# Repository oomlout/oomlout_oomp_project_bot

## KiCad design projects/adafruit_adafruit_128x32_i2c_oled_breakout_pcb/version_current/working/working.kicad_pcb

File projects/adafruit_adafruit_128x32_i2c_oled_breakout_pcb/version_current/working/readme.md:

# OOMP Project  
## Adafruit-128x32-I2C-OLED-Breakout-PCB  by adafruit  
  
oomp key: oomp_projects_flat_adafruit_adafruit_128x32_i2c_oled_breakout_pcb  
(snippet of original readme)  
  
- PCB for the Adafruit 128x32 I2C OLED breakout board  
  
<a href="http://www.adafruit.com/products/931"><br/>Click here to purchase one from the Adafruit shop</a>  
  
__Format is EagleCAD schematic and board layout__  
  
These displays are small, only about 1" diagonal, but very readable due to the high contrast of an OLED display. This display is made of 128x32 individual white OLED pixels, each one is turned on or off by the controller chip. Because the display makes its own light, no backlight is required. This reduces the power required to run the OLED and is why the display has such high contrast; we really like this miniature display for its crispness!  

The driver chip SSD1306, __communicates via I2C only.__ 3 pins are required to communicate with the chip in the OLED display, two of which are I2C data/clock pins.  
  
The OLED and driver require a 3.3V power supply and 3.3V logic levels for communication. To make it easier for our customers to use, we've added a 3.3v regulator and level shifter on board! This makes it compatible with any 5V microcontroller, such as the Arduino.  
  
The power requirements depend a little on how much of the display is lit but on average the display uses about 20mA from the 3.3V supply. Built into the OLED driver is a simple switch-cap charge pump that turns 3.3v-5v into a high voltage drive for the OLEDs, making it one of the easiest ways to get an OLED into your project!  
  
Of course, we wouldn't leave  
  full source readme at [readme_src.md](readme_src.md)  
  
source repo at: [https://github.com/adafruit/Adafruit-128x32-I2C-OLED-Breakout-PCB](https://github.com/adafruit/Adafruit-128x32-I2C-OLED-Breakout-PCB)  
## Board  

## Schematic  

[schematic pdf](working_schematic.pdf)  
## Images

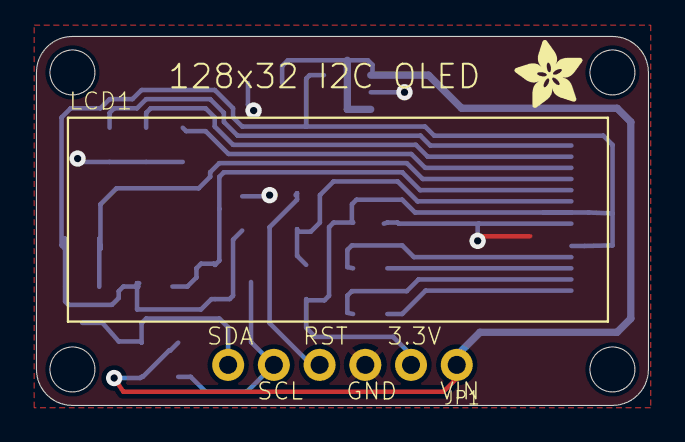
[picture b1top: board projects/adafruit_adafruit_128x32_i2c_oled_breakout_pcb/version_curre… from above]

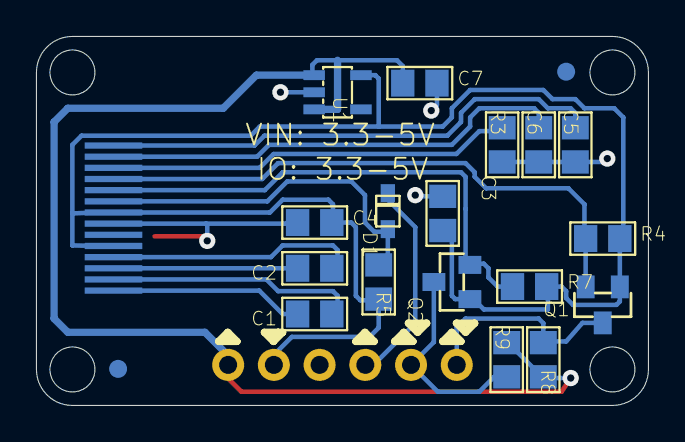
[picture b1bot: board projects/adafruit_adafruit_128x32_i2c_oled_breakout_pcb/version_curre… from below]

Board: 2 copper layers, 34.0 x 20.5 mm, 26 parts (19 on the bottom side), 16 nets.

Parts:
@HOLE0, @HOLE1, @HOLE2, @HOLE3: (no value)
C1, C2, C3, C4: 1uF; 0805
C5, C6, C7: 10uF; 0805
D1: 1N4148; SOD-323F
FID1, FID2: FIDUCIAL""; FIDUCIAL_1MM
JP1: 1X06_ROUND_70
LCD1: UG-2832HSWEG02_WRAPUNDER
Q1, Q2: BSS138; SOT23-WIDE
R3: 390K; 0805
R4, R5, R7, R8, R9: 10K; 0805
U1: RT9193; SOT23-5
U$16: ADAFRUIT_3.5MM

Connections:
3.3V: C3.2, C4.2, JP1.2, LCD1.5, LCD1.8, Q1.1, Q2.1, R4.2, R5.2, R7.2, U1.5
GND: C3.1, C4.1, C5.1, C6.1, C7.2, JP1.3, LCD1.7, R3.1, U1.2
unnamed: C1.2, LCD1.1
unnamed: C1.1, LCD1.2
unnamed: C2.2, LCD1.3
unnamed: C2.1, LCD1.4
unnamed: C6.2, LCD1.13
unnamed: C5.2, LCD1.14
unnamed: LCD1.12, R3.2
RES_3.3V: D1.A, LCD1.9, R5.1
RES_5.0V: D1.C, JP1.4
SCL_3.3V: LCD1.10, Q2.2, R7.1
SCL_5.0V: JP1.5, Q2.3, R9.1
SDA_3.3V: LCD1.11, Q1.2, R4.1
SDA_5.0V: JP1.6, Q1.3, R8.1
VIN: C7.1, JP1.1, R8.2, R9.2, U1.1, U1.3

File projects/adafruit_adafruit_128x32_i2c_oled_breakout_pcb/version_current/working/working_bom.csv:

"Id";"Designator";"Footprint";"Quantity";"Designation";"Supplier and ref";
1;"LCD1";"UG-2832HSWEG02_WRAPUNDER";1;"";;;
2;"@HOLE3,@HOLE0,@HOLE2,@HOLE1";"";4;"";;;
3;"JP1";"1X06_ROUND_70";1;"";;;
4;"U$16";"ADAFRUIT_3.5MM";1;"";;;
5;"C5,C7,C6";"0805";3;"10uF";;;
6;"C4,C3,C2,C1";"0805";4;"1uF";;;
7;"R3";"0805";1;"390K";;;
8;"FID1,FID2";"FIDUCIAL_1MM";2;"FIDUCIAL""";;;
9;"R5,R8,R4,R7,R9";"0805";5;"10K";;;
10;"D1";"SOD-323F";1;"1N4148";;;
11;"Q1,Q2";"SOT23-WIDE";2;"BSS138";;;
12;"U1";"SOT23-5";1;"RT9193";;;

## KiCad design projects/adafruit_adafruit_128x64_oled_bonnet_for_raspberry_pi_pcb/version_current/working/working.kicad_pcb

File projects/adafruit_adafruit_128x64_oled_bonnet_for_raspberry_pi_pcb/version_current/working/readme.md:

# OOMP Project  
## Adafruit-128x64-OLED-Bonnet-for-Raspberry-Pi-PCB  by adafruit  
  
oomp key: oomp_projects_flat_adafruit_adafruit_128x64_oled_bonnet_for_raspberry_pi_pcb  
(snippet of original readme)  
  
-- Adafruit 128x64 OLED Bonnet for Raspberry Pi PCB  
  
<a href="http://www.adafruit.com/products/3531"><br/>  
Click here to purchase one from the Adafruit shop</a>  
  
PCB files for the Adafruit 128x64 OLED Bonnet for Raspberry Pi. Format is EagleCAD schematic and board layout  
  
For more details, check out the product page at  
* http://www.adafruit.com/product/3531  
  
--- Description  
  
If you'd like a compact display, with buttons and a joystick - we've got what you're looking for. The Adafruit 128x64 OLED Bonnet for Raspberry Pi is the big sister to our mini PiOLED add-on. This version has 128x64 pixels (instead of 128x32) and a much larger screen besides. With the OLED display in the center, we had some space on either side so we added a 5-way joystick and two pushbuttons. Great for when you want to have a control interface for your project.  
  
These displays are small, only about 1.3" diagonal, but very readable due to the high contrast of an OLED display. This screen is made of 128x64 individual white OLED pixels and because the display makes its own light, no backlight is required. This reduces the power required to run the OLED and is why the display has such high contrast; we really like this miniature display for its crispness!  
  
Please note that this display is too small to act as a primary display for the Pi (e.g. it can't act like or display what would normally be on the HDMI screen). Instead, we recommend using pygame for drawi  
  full source readme at [readme_src.md](readme_src.md)  
  
source repo at: [https://github.com/adafruit/Adafruit-128x64-OLED-Bonnet-for-Raspberry-Pi-PCB](https://github.com/adafruit/Adafruit-128x64-OLED-Bonnet-for-Raspberry-Pi-PCB)  
## Board  

## Schematic  

[schematic pdf](working_schematic.pdf)  
## Images

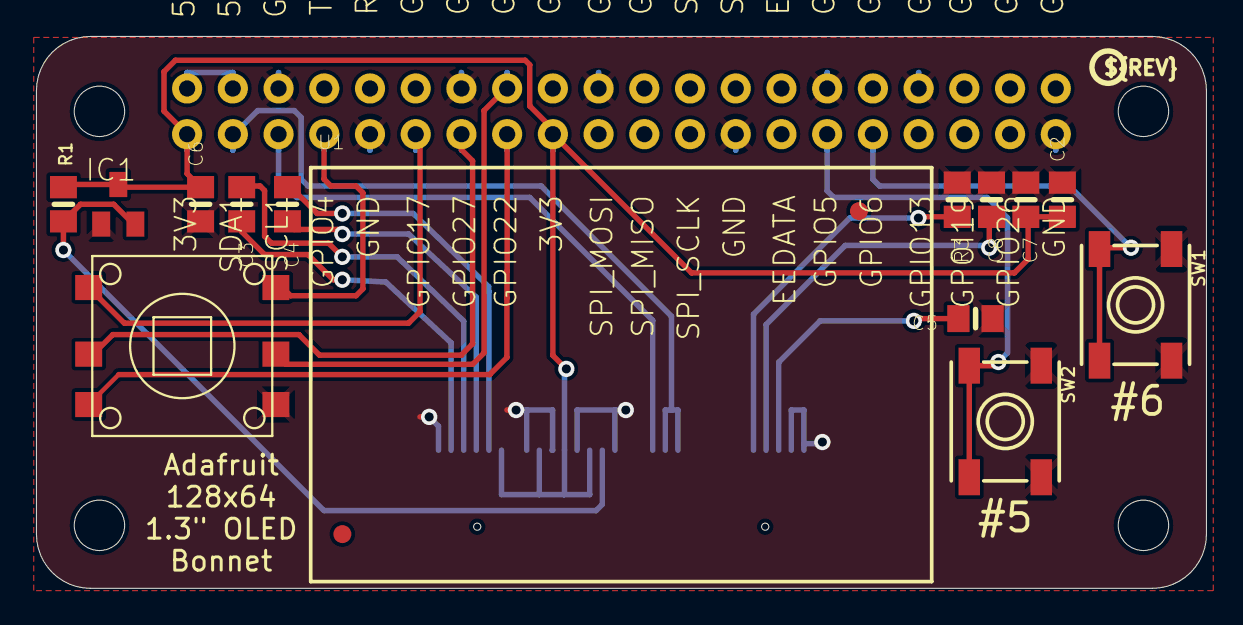
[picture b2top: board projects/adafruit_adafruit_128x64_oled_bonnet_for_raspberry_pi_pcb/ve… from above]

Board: 2 copper layers, 65.0 x 30.7 mm, 18 parts (0 on the bottom side), 20 nets.

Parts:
C2, C5: 10uF; 0805-NO
C3, C4, C6, C7, C8: 2.2uF; 0805-NO
FID1, FID2: FIDUCIAL_1MM
IC1: APX803; SOT23
R1: 10K; 0805-NO
R3: 390K; 0805-NO
RPI1: RASPBERRYPI_BPLUS_BONNET_THMSMT; PI_BONNET_THMSMT
SW1, SW2: EVQQ; EVQ-Q2_SMALLER
SW3: NAVSWITCHSKQUABAUE010; SKQUBAE010
U1: UG-2864HSWEG01; UG-2864HSWEG01_1.3_WRAPAROUND
U$2: PCBFEAT-REV-040

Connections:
3.3V: C2.1, C6.2, C7.2, IC1.3, R1.2, RPI1.1, RPI1.17, RPI1.S1, RPI1.S17, U1.6, U1.9, U1.11, U1.13
5.0V: RPI1.2, RPI1.4, RPI1.S2, RPI1.S4
GND: C2.2, C5.1, C6.1, C7.1, C8.1, IC1.1, R3.1, RPI1.6, RPI1.9, RPI1.14, RPI1.20, RPI1.25, RPI1.30, RPI1.34, RPI1.39, RPI1.S6, RPI1.S9, RPI1.S14, RPI1.S20, RPI1.S25, RPI1.S30, RPI1.S34, RPI1.S39, SW1.B, SW1.B', SW2.B, SW2.B', SW3.4, U1.1, U1.8, U1.10, U1.12, U1.15, U1.29, U1.30
GPIO4: RPI1.7, RPI1.S7, SW3.6
GPIO5: RPI1.29, RPI1.S29, SW2.A, SW2.A'
GPIO6: RPI1.31, RPI1.S31, SW1.A, SW1.A'
GPIO17: RPI1.11, RPI1.S11, SW3.1
GPIO22: RPI1.15, RPI1.S15, SW3.3
GPIO23: RPI1.16, RPI1.S16, SW3.5
GPIO27: RPI1.13, RPI1.S13, SW3.2
unnamed: R3.2, U1.26
unnamed: C3.2, U1.2
unnamed: C3.1, U1.3
unnamed: C4.2, U1.4
unnamed: C4.1, U1.5
unnamed: C5.2, U1.28
unnamed: C8.2, U1.27
RST: IC1.2, R1.1, U1.14
SCL: RPI1.5, RPI1.S5, U1.18
SDA: RPI1.3, RPI1.S3, U1.19, U1.20

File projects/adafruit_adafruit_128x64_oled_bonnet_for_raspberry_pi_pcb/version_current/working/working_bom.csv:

Row,Description,Part,References,Value,Footprint,Quantity Per PCB,Status,Datasheet
1,,CAP_CERAMIC0805-NOOUTLINE,C3 C4 C6 C7 C8,2.2uF,0805-NO,5, ,
2,,CAP_CERAMIC0805-NOOUTLINE,C2 C5,10uF,0805-NO,2, ,
3,,AXP083-SAG,IC1,APX803,SOT23,1, ,
4,,RESISTOR0805_NOOUTLINE,R1,10K,0805-NO,1, ,
5,,RESISTOR0805_NOOUTLINE,R3,390K,0805-NO,1, ,
6,,RASPBERRYPI_BPLUS_BONNET_THMSMT,RPI1,RASPBERRYPI_BPLUS_BONNET_THMSMT,PI_BONNET_THMSMT,1, ,
7,,SWITCH_TACT_SMT_EVQQ2_SMALL,SW1 SW2,EVQQ,EVQ-Q2_SMALLER,2, ,
8,,NAVSWITCHSKQUABAUE010,SW3,NAVSWITCHSKQUABAUE010,SKQUBAE010,1, ,
9,,DISP_OLED_UG-2864HSWEG01,U1,UG-2864HSWEG01,UG-2864HSWEG01_1.3_WRAPAROUND,1, ,





Project info:
Schematic:,working
Variant:,default
Revision:,
Date:,2023-08-02_17-08-31
KiCad Version:,7.0.6-7.0.6~ubuntu22.04.1
Statistics:
Component Groups:,9
Component Count:,15 (0 SMD/ 0 THT)
Fitted Components:,15 (0 SMD/ 0 THT)
Number of PCBs:,1
Total Components:,15

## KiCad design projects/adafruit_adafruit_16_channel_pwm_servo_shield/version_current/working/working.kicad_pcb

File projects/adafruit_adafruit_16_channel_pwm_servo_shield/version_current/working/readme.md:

# Adafruit-16-channel-PWM-Servo-Shield by adafruit  
This is a harvested standardized copy of a project from github.  
The original project can be found at:  
https://github.com/adafruit/Adafruit-16-channel-PWM-Servo-Shield  
Please consult that link for additional, details, files, and license information.  
Note: It was auto harvested and if the original repo had more than one board file or anything out of the ordinary the files here are likely not representative.

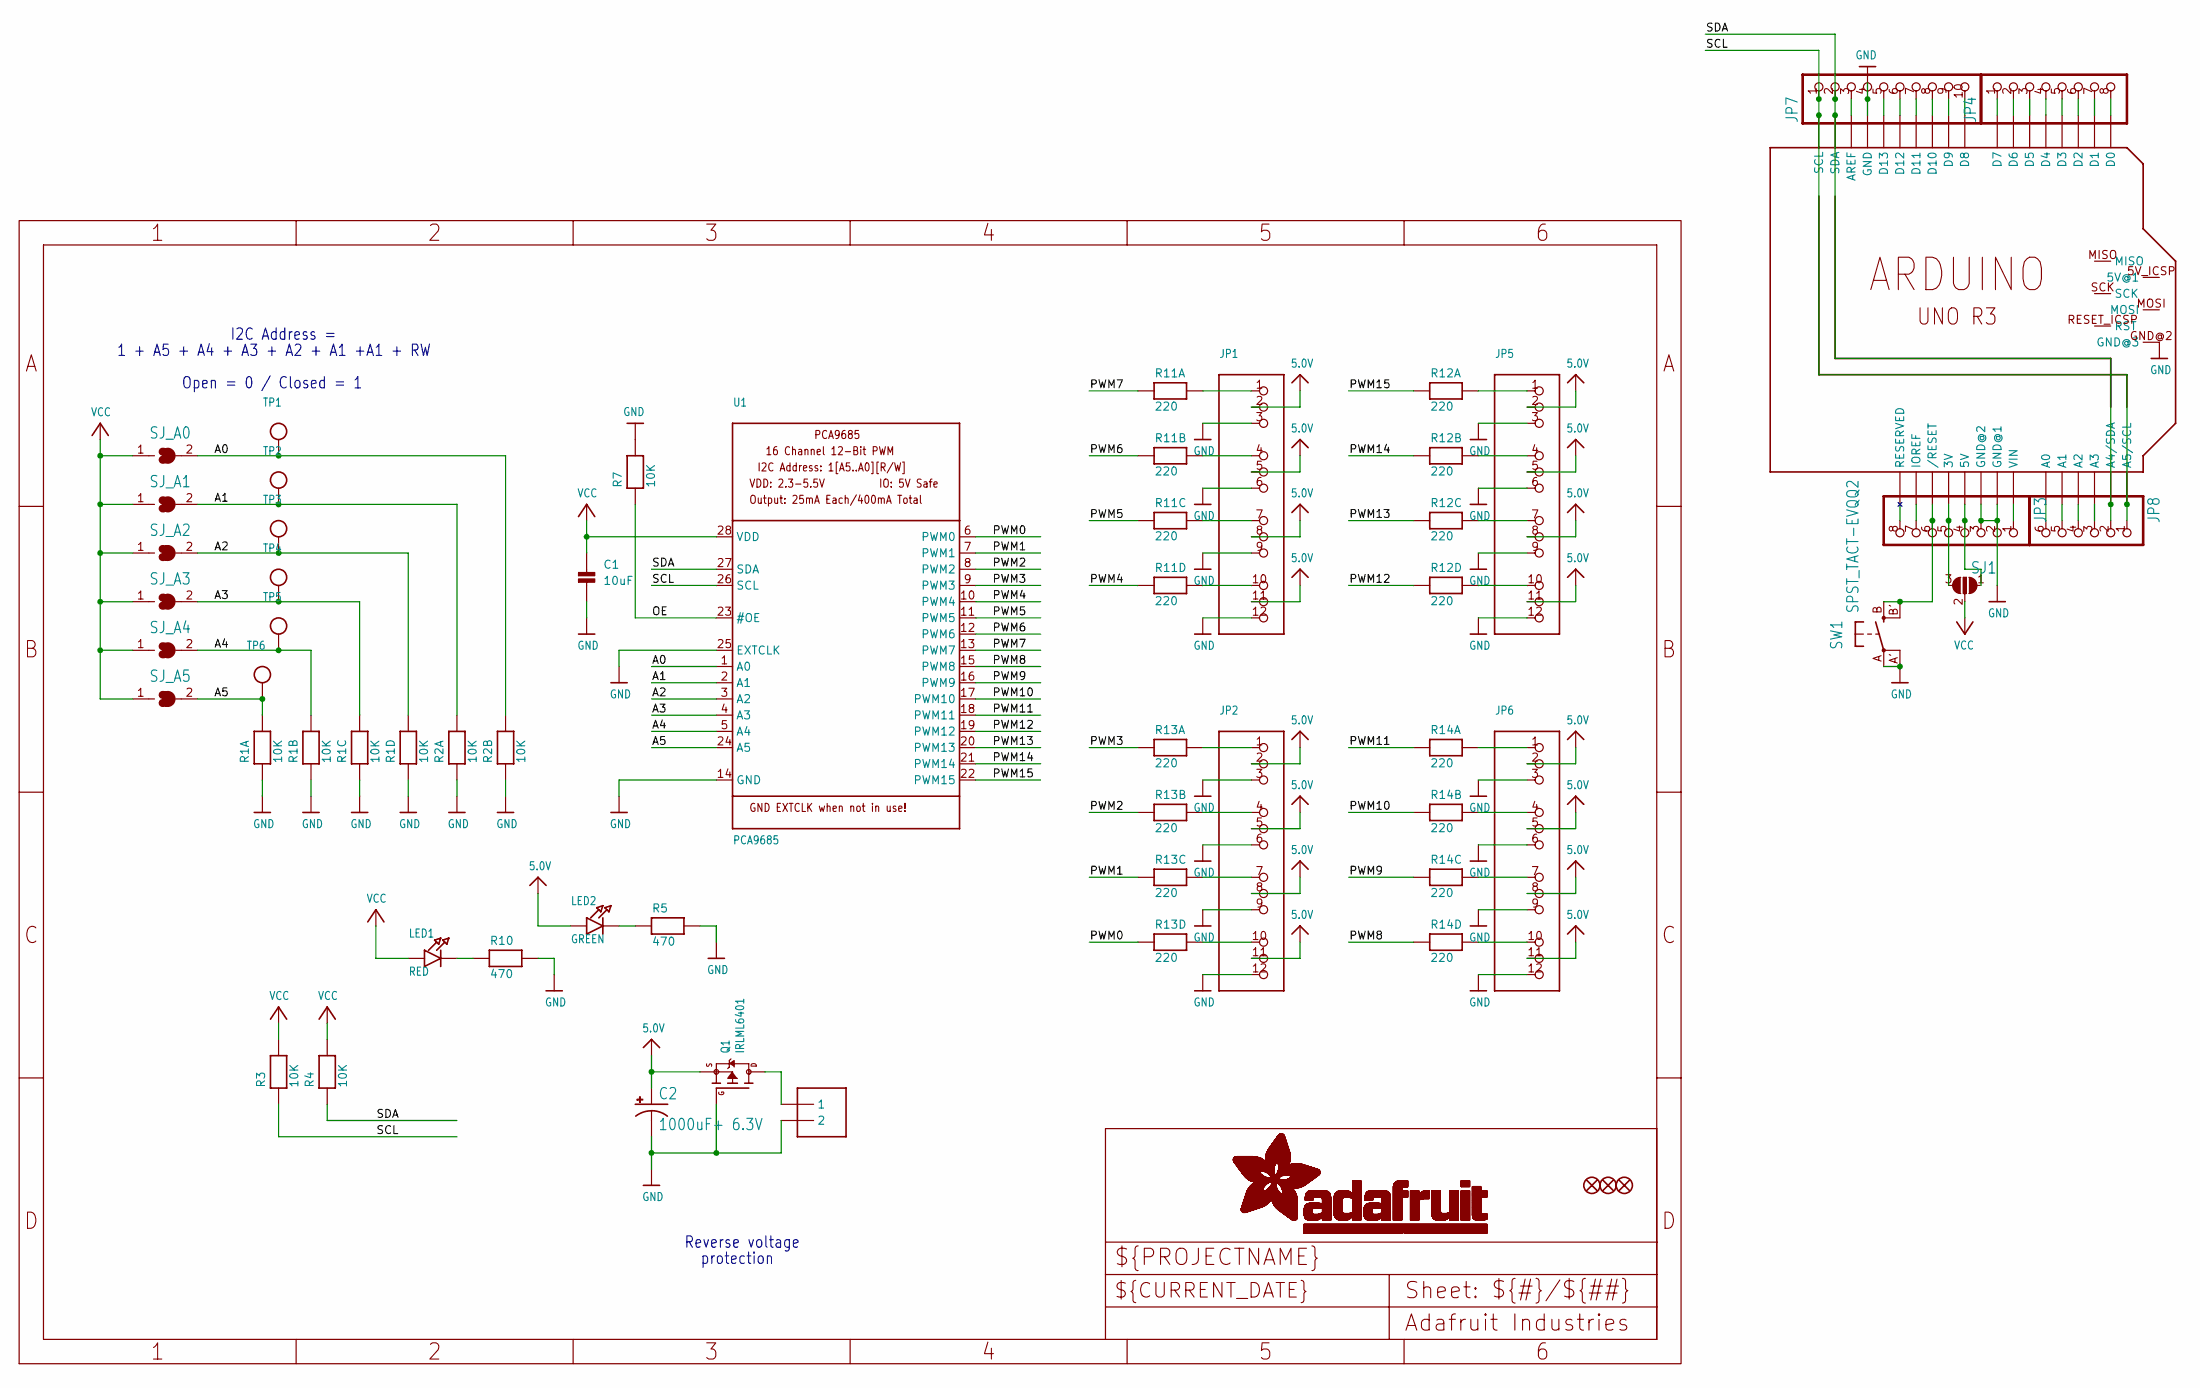
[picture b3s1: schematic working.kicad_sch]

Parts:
C1: 10uF; 0805
C2: 1000uF+ 6.3V; E3,5-10
FID1, FID2, FID3: FIDUCIAL""; FIDUCIAL_1MM
J1: TERMBLOCK_1X2-3.5MM; 1X2-3.5MM
JP1, JP2, JP5, JP6: HEADER-3X04; 3X04
JP3, JP4: PINHD-1X8CLEANBIG; 1X08-CLEANBIG
JP7: HEADER-1X1070MIL; 1X10_ROUND70
JP8: PINHD-1X6CB; 1X06-CLEANBIG
LED1: RED; CHIPLED_0805
LED2: GREEN; CHIPLED_0805
Q1: IRLML6401; SOT23-WIDE
R1, R2: 10K; RESPACK_4X0603
R3, R4, R7: 10K; 0805
R5, R10: 470; 0805
R11, R12, R13, R14: 220; RESPACK_4X0603
SJ1: SOLDERJUMPER_2WAY; SOLDERJUMPER_2WAY_OPEN_NOPASTE
SJ_A0, SJ_A1, SJ_A2, SJ_A3, SJ_A4, SJ_A5: SOLDERJUMPERREFLOW_NOPASTE; SOLDERJUMPER_REFLOW_NOPASTE
SW1: SPST_TACT-EVQQ2; EVQ-Q2
TP1, TP2, TP3, TP4, TP5, TP6: TESTPOINTROUND2MM; TESTPOINT_ROUND_2MM
U1: PCA9685; TSSOP28
U$44: ARDUINO_R3_ICSP; ARDUINOR3_ICSP

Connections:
5.0V: C2.+, JP1.2, JP1.5, JP1.8, JP1.11, JP2.2, JP2.5, JP2.8, JP2.11, JP5.2, JP5.5, JP5.8, JP5.11, JP6.2, JP6.5, JP6.8, JP6.11, LED2.A, Q1.2 (S)
A0: R2.7 (2), SJ_A0.2, TP1.P$1, U1.1 (A0)
A1: R2.8 (2), SJ_A1.2, TP2.P$1, U1.2 (A1)
A2: R1.5 (2), SJ_A2.2, TP3.P$1, U1.3 (A2)
A3: R1.6 (2), SJ_A3.2, TP4.P$1, U1.4 (A3)
A4: R1.7 (2), SJ_A4.2, TP5.P$1, U1.5 (A4)
A5: R1.8 (2), SJ_A5.2, TP6.P$1, U1.24 (A5)
GND: C1.2, C2.-, J1.2, JP1.3, JP1.6, JP1.9, JP1.12, JP2.3, JP2.6, JP2.9, JP2.12, JP3.2, JP3.3, JP5.3, JP5.6, JP5.9, JP5.12, JP6.3, JP6.6, JP6.9, JP6.12, JP7.4, Q1.1 (G), R1.1, R1.2 (1), R1.3 (1), R1.4 (1), R2.1, R2.2 (1), R5.2, R7.2, R10.2, SW1.A, SW1.A' (P1), U1.14 (GND), U1.25 (EXTCLK), U$44.GND, U$44.GND@1 (GND@2), U$44.GND@2 (GND@3), U$44.GND@3 (GND@1)
unnamed: LED1.C, R10.1
unnamed: JP1.4, R11.7 (2)
unnamed: JP1.1, R11.8 (2)
unnamed: JP1.7, R11.6 (2)
unnamed: JP1.10, R11.5 (2)
unnamed: JP2.1, R13.8 (2)
unnamed: JP2.4, R13.7 (2)
unnamed: JP2.7, R13.6 (2)
unnamed: JP2.10, R13.5 (2)
unnamed: JP6.10, R14.5 (2)
unnamed: JP6.7, R14.6 (2)
unnamed: JP6.4, R14.7 (2)
unnamed: JP6.1, R14.8 (2)
unnamed: JP5.10, R12.5 (2)
unnamed: JP5.7, R12.6 (2)
unnamed: JP5.4, R12.7 (2)
unnamed: JP5.1, R12.8 (2)
unnamed: JP3.1, U$44.VIN
unnamed: LED2.C, R5.1
unnamed: JP3.5, SJ1.3, U$44.3V
unnamed: JP3.4, SJ1.1, U$44.5V
unnamed: JP3.7, U$44.IOREF
unnamed: JP3.8, U$44.RESERVED
unnamed: JP4.1, U$44.D7
unnamed: JP4.2, U$44.D6
unnamed: JP4.3, U$44.D5
unnamed: JP4.4, U$44.D4
unnamed: JP4.5, U$44.D3
unnamed: JP4.6, U$44.D2
unnamed: JP4.7, U$44.D1
unnamed: JP4.8, U$44.D0
unnamed: JP7.3, U$44.AREF
unnamed: JP7.5, U$44.D13
unnamed: JP7.6, U$44.D12
unnamed: JP7.7, U$44.D11
unnamed: JP7.8, U$44.D10
unnamed: JP7.9, U$44.D9
unnamed: JP7.10, U$44.D8
unnamed: JP8.3, U$44.A3
unnamed: JP8.4, U$44.A2
unnamed: JP8.5, U$44.A1
unnamed: JP8.6, U$44.A0
unnamed: JP3.6, SW1.B (S), SW1.B' (S1), U$44.RESET (/RESET)
OE: R7.1, U1.23 (#OE)
PWM0: R13.4 (1), U1.6 (PWM0)
PWM1: R13.3 (1), U1.7 (PWM1)
PWM2: R13.2 (1), U1.8 (PWM2)
PWM3: R13.1, U1.9 (PWM3)
PWM4: R11.4 (1), U1.10 (PWM4)
PWM5: R11.3 (1), U1.11 (PWM5)
PWM6: R11.2 (1), U1.12 (PWM6)
PWM7: R11.1, U1.13 (PWM7)
PWM8: R14.4 (1), U1.15 (PWM8)
PWM9: R14.3 (1), U1.16 (PWM9)
PWM10: R14.2 (1), U1.17 (PWM10)
PWM11: R14.1, U1.18 (PWM11)
PWM12: R12.4 (1), U1.19 (PWM12)
PWM13: R12.3 (1), U1.20 (PWM13)
PWM14: R12.2 (1), U1.21 (PWM14)
PWM15: R12.1, U1.22 (PWM15)
PWRIN: J1.1, Q1.3 (D)
SCL: JP7.1, JP8.1, R3.1, U1.26 (SCL), U$44.A5 (A5/SCL), U$44.SCL
SDA: JP7.2, JP8.2, R4.1, U1.27 (SDA), U$44.A4 (A4/SDA), U$44.SDA
VCC: C1.1, LED1.A, R3.2, R4.2, SJ1.2, SJ_A0.1, SJ_A1.1, SJ_A2.1, SJ_A3.1, SJ_A4.1, SJ_A5.1, U1.28 (VDD)

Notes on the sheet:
protection
I2C Address =
Reverse voltage
Open = 0 / Closed = 1
1 + A5 + A4 + A3 + A2 + A1 +A1 + RW

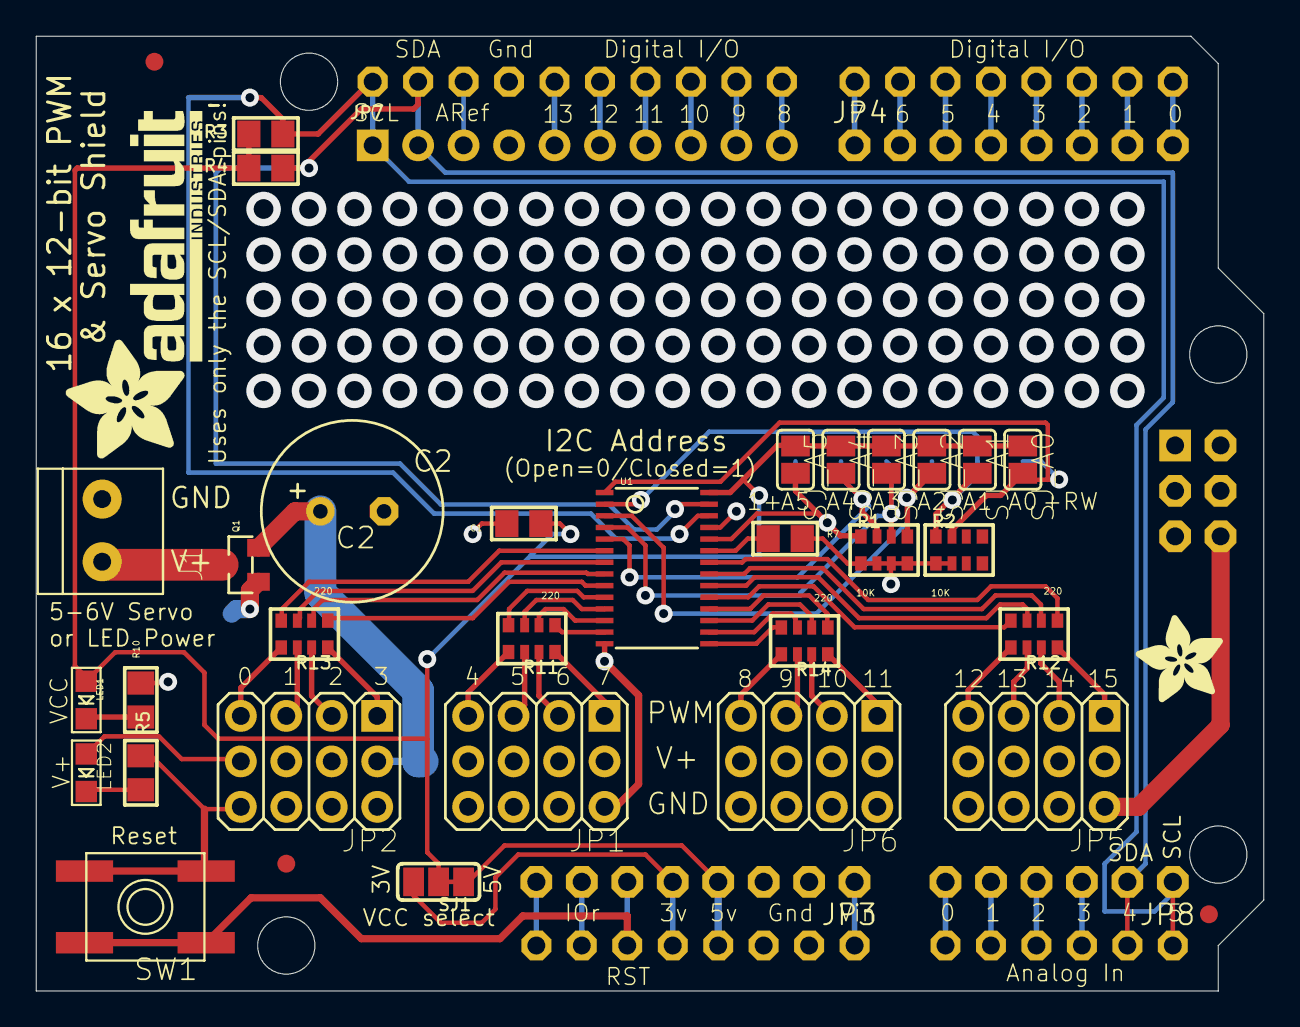
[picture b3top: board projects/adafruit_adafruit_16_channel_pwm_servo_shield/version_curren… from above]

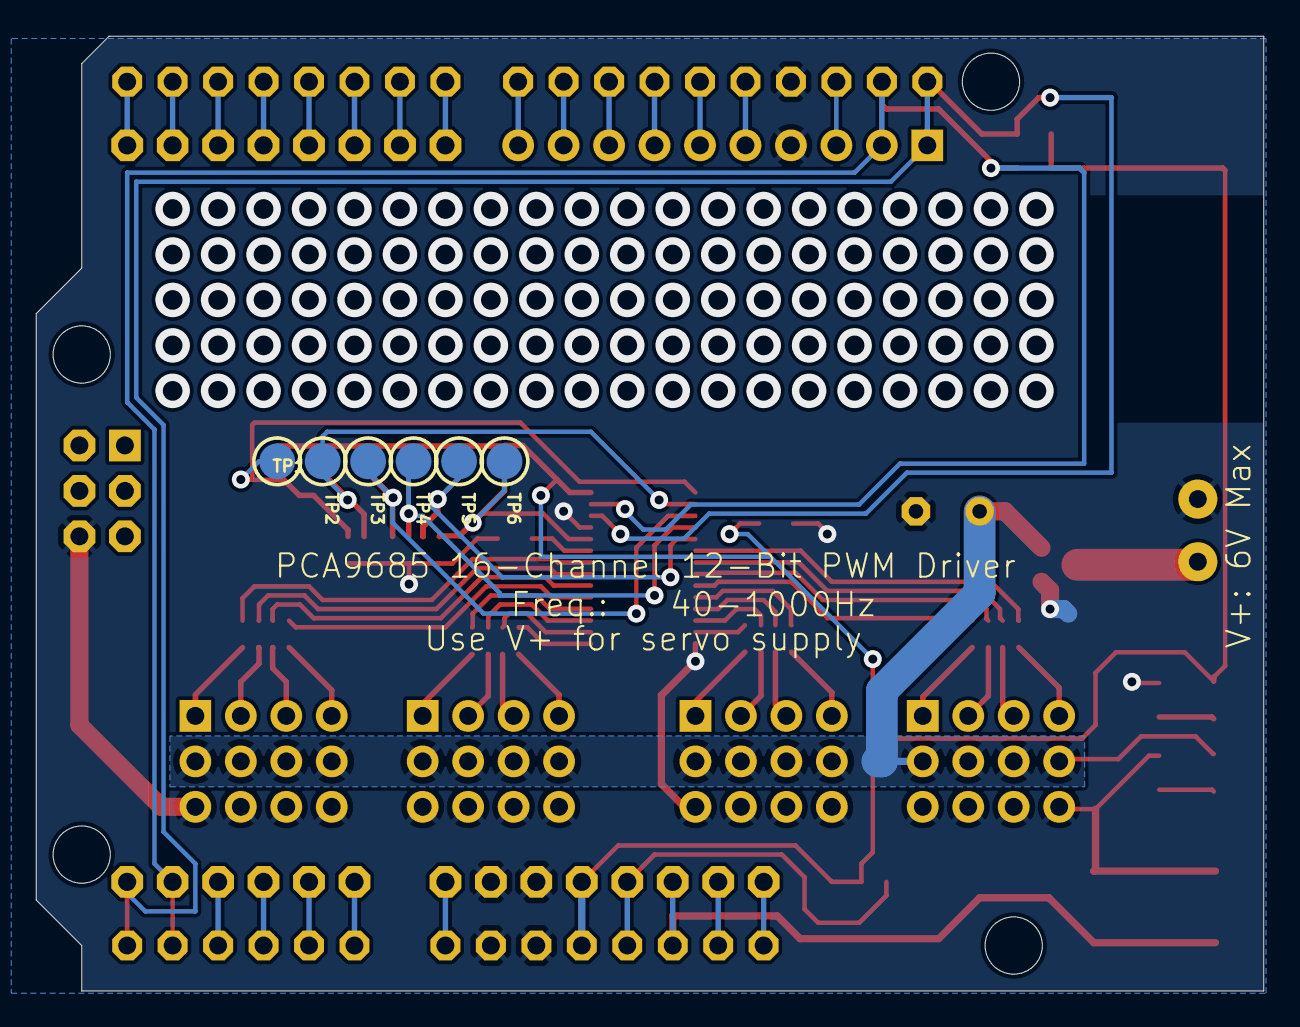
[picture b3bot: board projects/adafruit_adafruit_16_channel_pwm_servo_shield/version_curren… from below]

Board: 2 copper layers, 68.6 x 53.3 mm, 50 parts (6 on the bottom side), 72 nets.

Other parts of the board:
@HOLE0, @HOLE1, @HOLE2, @HOLE3: (no value)
U$51: ADAFRUIT_5MM
U$54: ADAFRUIT_TEXT_20MM

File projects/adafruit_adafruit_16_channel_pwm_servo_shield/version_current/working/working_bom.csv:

Row,Description,Part,References,Value,Footprint,Quantity Per PCB,Status,Datasheet
1,,CAP_CERAMIC0805,C1,10uF,0805,1, ,
2,,CPOL-USE3.5-10,C2,1000uF+ 6.3V,"E3,5-10",1, ,
3,,TERMBLOCK_1X2-3.5MM,J1,TERMBLOCK_1X2-3.5MM,1X2-3.5MM,1, ,
4,,HEADER-1X1070MIL,JP7,HEADER-1X1070MIL,1X10_ROUND70,1, ,
5,,HEADER-3X04,JP1 JP2 JP5 JP6,HEADER-3X04,3X04,4, ,
6,,PINHD-1X6CB,JP8,PINHD-1X6CB,1X06-CLEANBIG,1, ,
7,,PINHD-1X8CLEANBIG,JP3 JP4,PINHD-1X8CLEANBIG,1X08-CLEANBIG,2, ,
8,,LED0805,LED2,GREEN,CHIPLED_0805,1, ,
9,,LED0805,LED1,RED,CHIPLED_0805,1, ,
10,,MOSFET-PWIDE,Q1,IRLML6401,SOT23-WIDE,1, ,
11,,RESISTOR_4PACK,R11 R12 R13 R14,220,RESPACK_4X0603,4, ,
12,,RESISTOR0805,R5 R10,470,0805,2, ,
13,,RESISTOR_4PACK,R1 R2,10K,RESPACK_4X0603,2, ,
14,,RESISTOR0805,R3 R4 R7,10K,0805,3, ,
15,,SPST_TACT-EVQQ2,SW1,SPST_TACT-EVQQ2,EVQ-Q2,1, ,
16,,PCA9685,U1,PCA9685,TSSOP28,1, ,
17,,ARDUINO_R3_ICSP,U$44,ARDUINO_R3_ICSP,ARDUINOR3_ICSP,1, ,





Project info:
Schematic:,working
Variant:,default
Revision:,
Date:,2023-08-02_17-08-31
KiCad Version:,7.0.6-7.0.6~ubuntu22.04.1
Statistics:
Component Groups:,17
Component Count:,28 (0 SMD/ 0 THT)
Fitted Components:,28 (0 SMD/ 0 THT)
Number of PCBs:,1
Total Components:,28

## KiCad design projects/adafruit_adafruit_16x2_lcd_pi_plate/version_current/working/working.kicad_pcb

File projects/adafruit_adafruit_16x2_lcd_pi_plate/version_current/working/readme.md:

# OOMP Project  
## Adafruit-16x2-LCD-Pi-Plate  by adafruit  
  
oomp key: oomp_projects_flat_adafruit_adafruit_16x2_lcd_pi_plate  
(snippet of original readme)  
  
- PCB files for Adafruit 16x2 LCD Pi Plate for Raspberry Pi  
  
<a href="http://www.adafruit.com/products/1110"><br/>Click here to purchase one from the Adafruit shop</a>  
  
* https://www.adafruit.com/product/1110  
* https://www.adafruit.com/product/1115  
* http://www.adafruit.com/products/1109  
  
This new Adafruit Pi Plate makes it easy to use a blue and white 16x2 Character LCD. [We really like the 16x2 Character LCDs we stock in the shop](http://www.adafruit.com/products/181). Unfortunately, these LCDs do require quite a few digital pins, 6 to control the LCD and then another 1 to control the backlight for a total of 7 pins. That's nearly all the GPIO available on a Pi!  
  
With this in mind, we wanted to make it easier for people to get these LCD into their projects so we devised a Pi plate that lets you control __a 16x2 Character LCD, up to 3 backlight pins AND 5 keypad pins using only the two I2C pins on the R-Pi!__ The best part is you don't really lose those two pins either, since you can stick i2c-based sensors, RTCs, etc and have them share the I2C bus. This is a super slick way to add a display without all the wiring hassle.  
  
__New, we've updated this Pi plate so the buttons on on the right side, which makes it a little more mechanically stable__  
  
This pi plate is perfect for when you want to build a stand-alone project with its own user interface. The 4 directional buttons plus select button allows basic control without havin  
  full source readme at [readme_src.md](readme_src.md)  
  
source repo at: [https://github.com/adafruit/Adafruit-16x2-LCD-Pi-Plate](https://github.com/adafruit/Adafruit-16x2-LCD-Pi-Plate)  
## Board  

## Schematic  

[schematic pdf](working_schematic.pdf)  
## Images

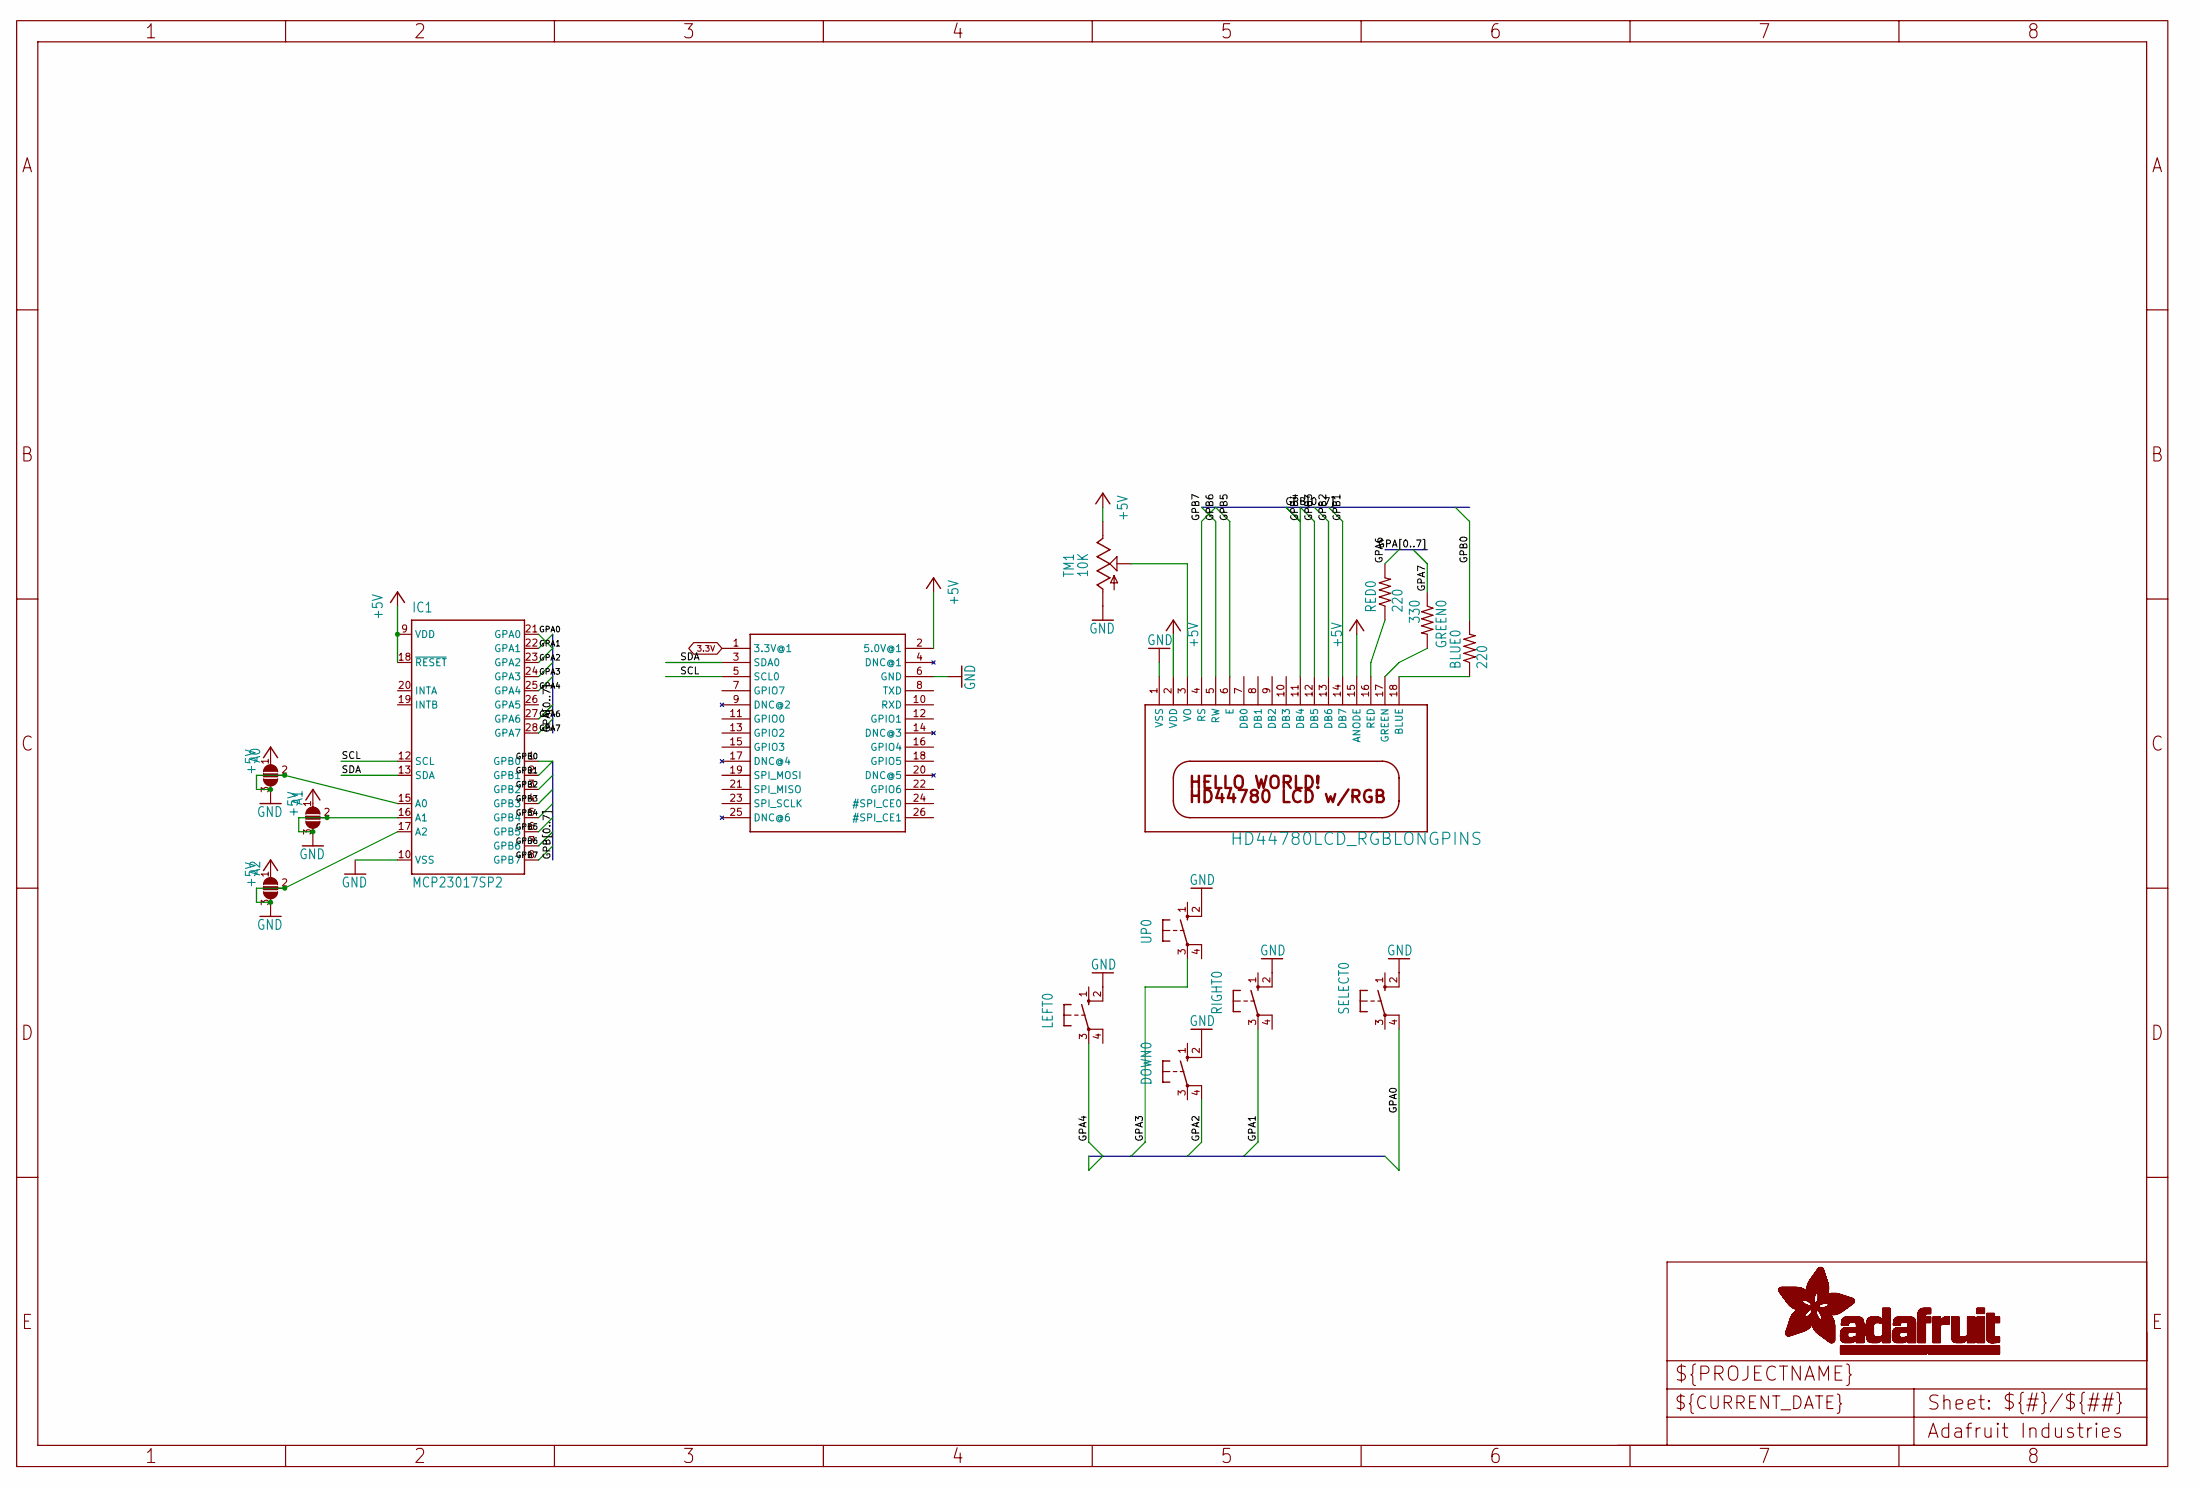
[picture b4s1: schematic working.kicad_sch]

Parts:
A0, A1, A2: SOLDERJUMPER_2WAY; SOLDERJUMPER_2WAY_OPEN_NOPASTE
BLUE0: 220; 0207_10
DOWN0: 10-XX; B3F-10XX
GREEN0: 330; 0207_10
IC1: MCP23017SP2; DIL28-3-ROUND
LEFT0: 10-XX; B3F-10XX
RED0: 220; 0207_10
RIGHT0: 10-XX; B3F-10XX
SELECT0: 10-XX; B3F-10XX
TM1: 10K; 6MM
U$1: HD44780LCD_RGBLONGPINS; LCD1602-RGB
U$4: RASPBERRYPI_BB; RASBERRYPI_SHIELD
UP0: 10-XX; B3F-10XX

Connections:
+5V: A0.1, A1.1, A2.1, IC1.9 (VDD), IC1.18 (~RESET), TM1.E, U$1.2 (VDD), U$1.15 (ANODE), U$4.2 (5.0V@1)
GND: A0.2, A0.3, A1.2, A1.3, A2.2, A2.3, DOWN0.2 (S1), IC1.10 (VSS), IC1.15 (A0), IC1.16 (A1), IC1.17 (A2), LEFT0.2 (S1), RIGHT0.2 (S1), SELECT0.2 (S1), TM1.A, U$1.1 (VSS), U$4.6 (GND), UP0.2 (S1)
GPA0: IC1.21 (GPA0), SELECT0.4 (P1)
GPA1: IC1.22 (GPA1), RIGHT0.3
GPA2: DOWN0.4 (P1), IC1.23 (GPA2)
GPA3: IC1.24 (GPA3), UP0.3
GPA4: IC1.25 (GPA4), LEFT0.3
GPA6: IC1.27 (GPA6), RED0.2
GPA7: GREEN0.1, IC1.28 (GPA7)
GPB0: BLUE0.2, IC1.1 (GPB0)
GPB1: IC1.2 (GPB1), U$1.14 (DB7)
GPB2: IC1.3 (GPB2), U$1.13 (DB6)
GPB3: IC1.4 (GPB3), U$1.12 (DB5)
GPB4: IC1.5 (GPB4), U$1.11 (DB4)
GPB5: IC1.6 (GPB5), U$1.6 (E)
GPB6: IC1.7 (GPB6), U$1.5 (RW)
GPB7: IC1.8 (GPB7), U$1.4 (RS)
unnamed: BLUE0.1, U$1.18 (BLUE)
unnamed: GREEN0.2, U$1.17 (GREEN)
unnamed: RED0.1, U$1.16 (RED)
unnamed: TM1.S, U$1.3 (VO)
SCL: IC1.12 (SCL), U$4.5 (SCL0)
SDA: IC1.13 (SDA), U$4.3 (SDA0)

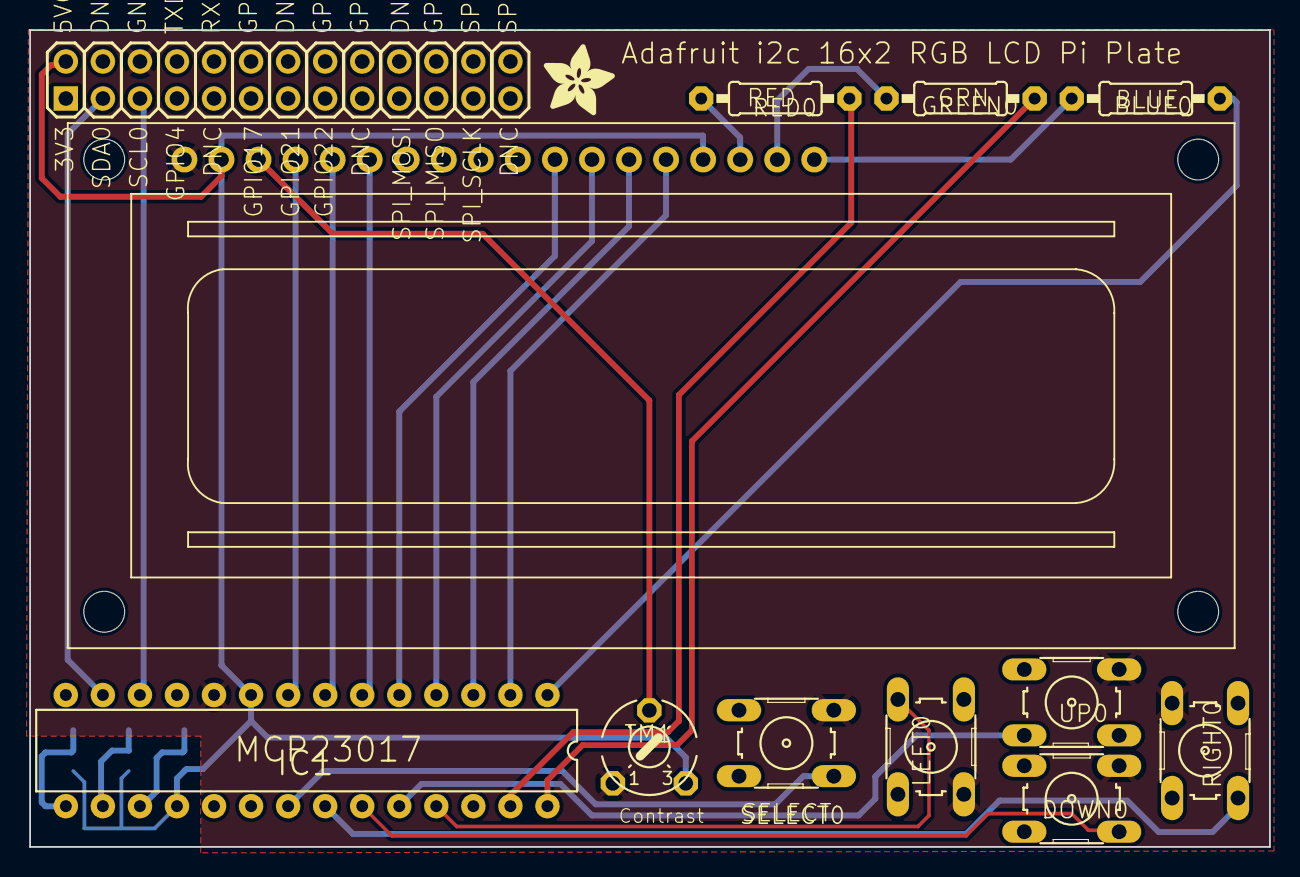
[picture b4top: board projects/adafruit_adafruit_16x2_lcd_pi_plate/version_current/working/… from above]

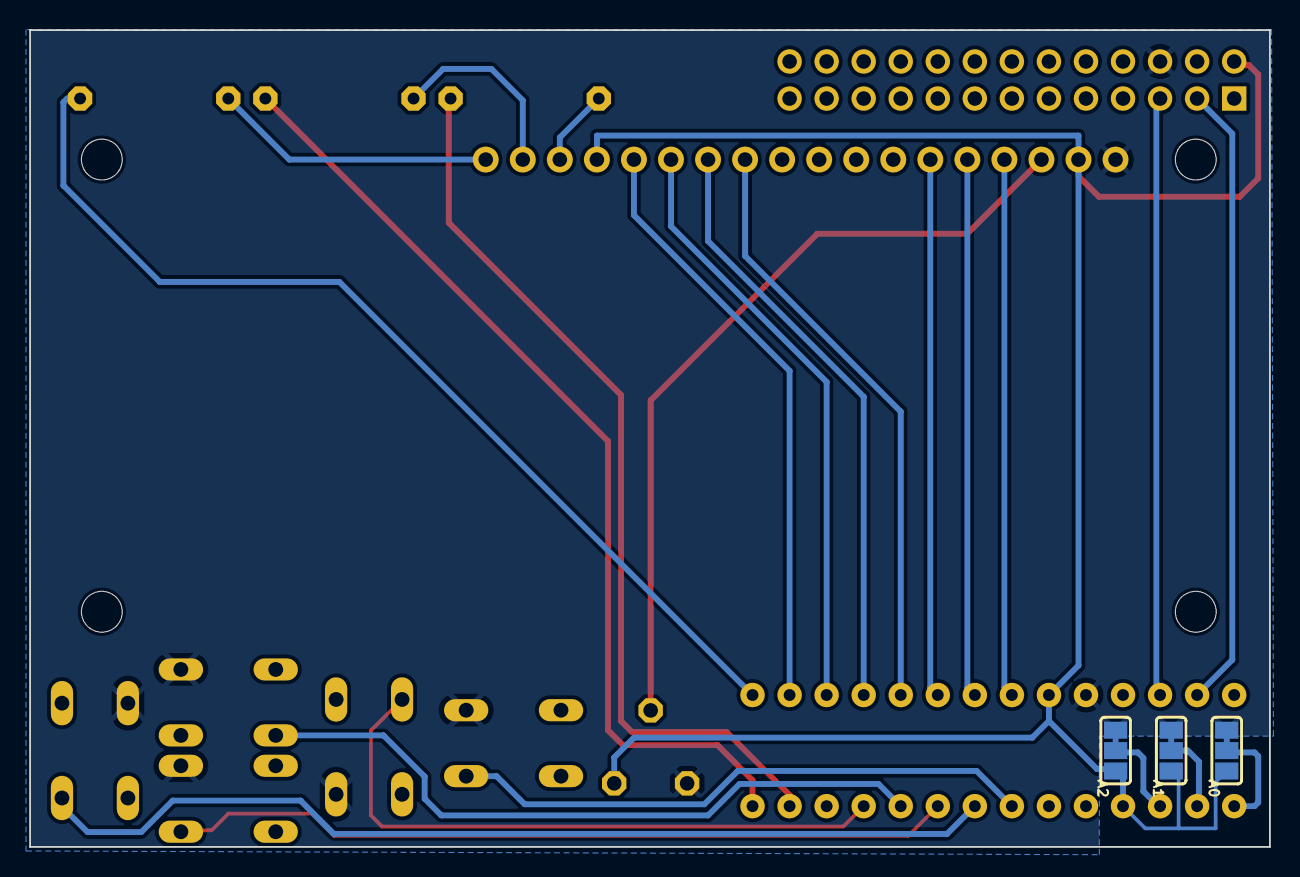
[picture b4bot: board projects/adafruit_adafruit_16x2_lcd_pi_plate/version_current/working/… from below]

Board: 16 copper layers, 85.0 x 56.0 mm, 16 parts (3 on the bottom side), 23 nets.

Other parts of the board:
U$2: ADAFRUIT_5MM

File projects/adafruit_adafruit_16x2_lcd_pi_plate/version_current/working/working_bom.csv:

Row,Description,Part,References,Value,Footprint,Quantity Per PCB,Status,Datasheet
1,,R-US_0207/10,BLUE0 RED0,220,0207_10,2, ,
2,,10-XX,DOWN0 LEFT0 RIGHT0 SELECT0 UP0,10-XX,B3F-10XX,5, ,
3,,R-US_0207/10,GREEN0,330,0207_10,1, ,
4,,MCP23017SP2,IC1,MCP23017SP2,DIL28-3-ROUND,1, ,
5,,TRIM,TM1,10K,6MM,1, ,
6,,HD44780LCD_RGBLONGPINS,U$1,HD44780LCD_RGBLONGPINS,LCD1602-RGB,1, ,
7,,RASPBERRYPI_BB,U$4,RASPBERRYPI_BB,RASBERRYPI_SHIELD,1, ,





Project info:
Schematic:,working
Variant:,default
Revision:,
Date:,2023-08-02_17-08-32
KiCad Version:,7.0.6-7.0.6~ubuntu22.04.1
Statistics:
Component Groups:,7
Component Count:,12 (0 SMD/ 0 THT)
Fitted Components:,12 (0 SMD/ 0 THT)
Number of PCBs:,1
Total Components:,12
